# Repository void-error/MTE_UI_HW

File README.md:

# MTE_UI_HW
User Interface hardware common to all Modular Test Equipment projects

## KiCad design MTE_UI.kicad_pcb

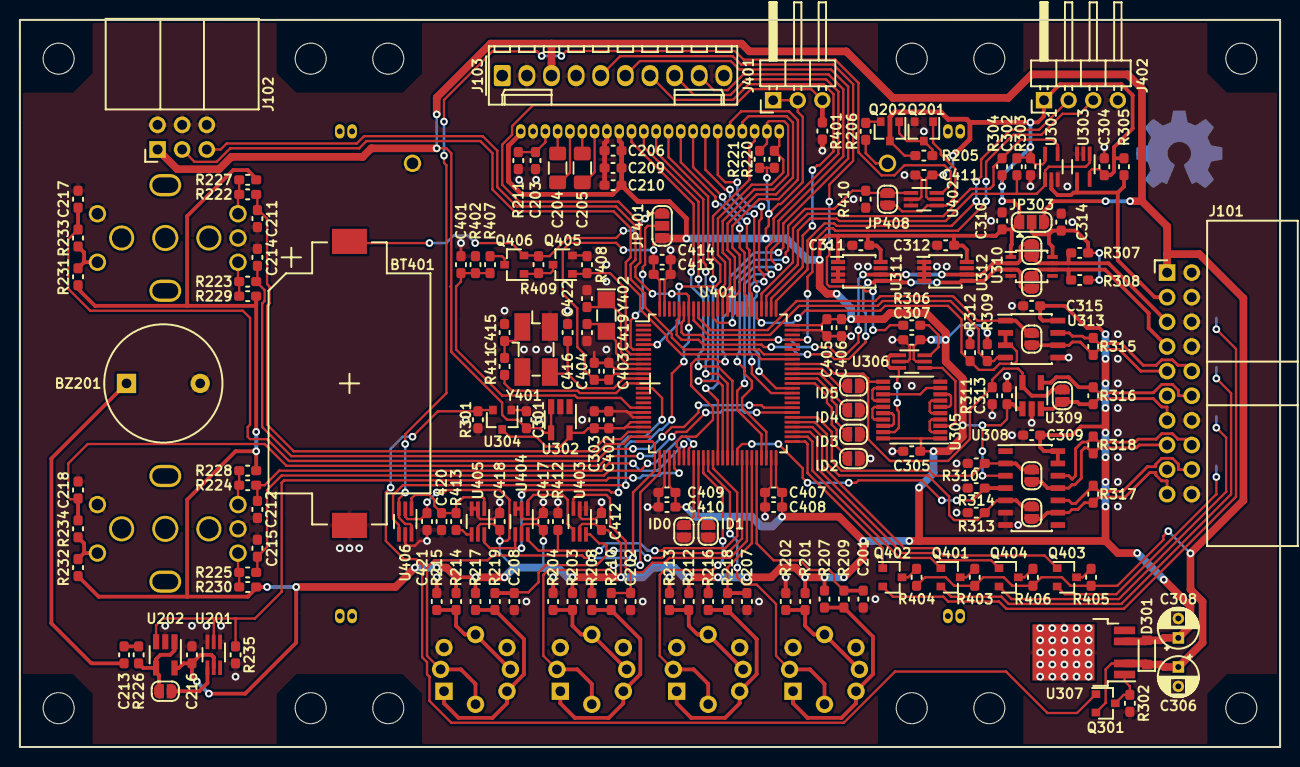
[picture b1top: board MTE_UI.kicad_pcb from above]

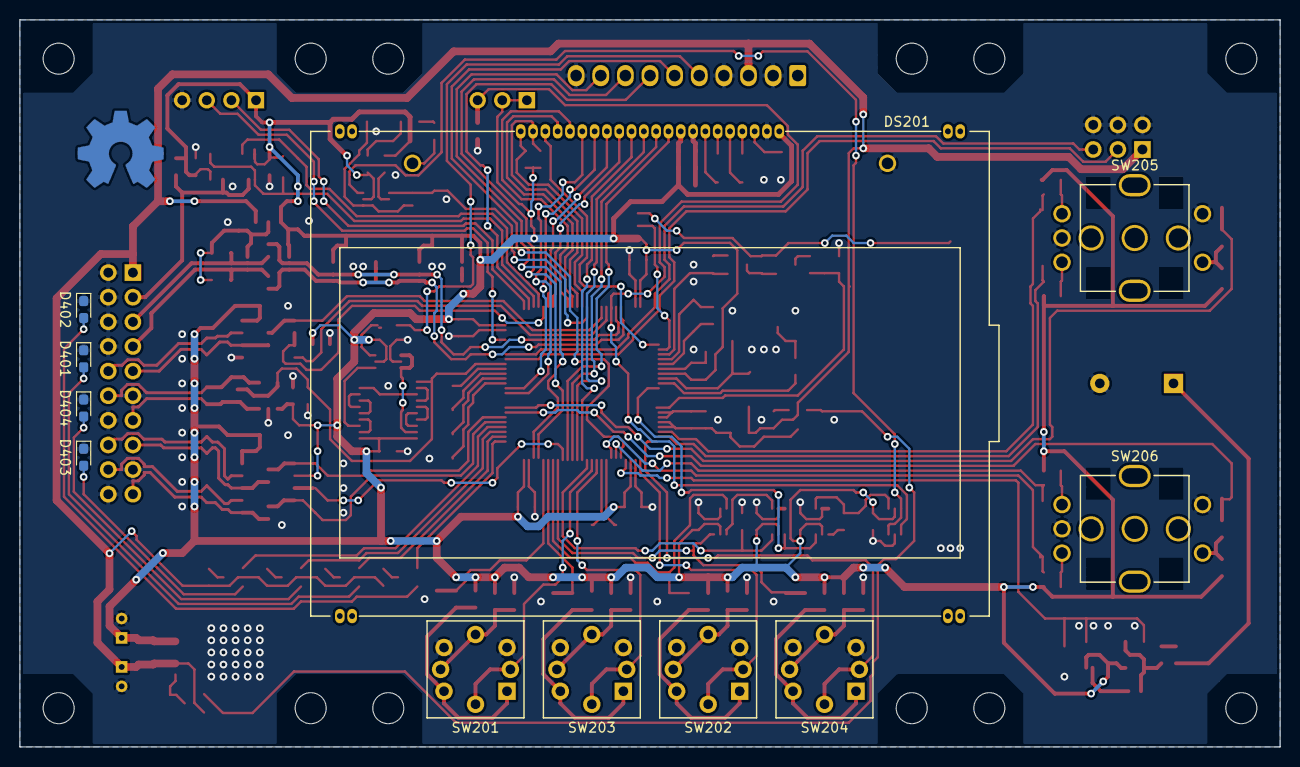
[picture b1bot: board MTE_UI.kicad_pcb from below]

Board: 2 copper layers, 130.0 x 75.0 mm, 201 parts (12 on the bottom side), 140 nets.

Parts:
BT401: Battery_Cell; BatteryHolder_Keystone_1060_1x2032
BZ201: Buzzer; Buzzer_12x9.5RM7.6
C201, C202, C207, C208, C211, C212, C214, C215, C217, C218, C401, C402: 10n; C_0603_1608Metric_Pad1.05x0.95mm_HandSolder
C203: 330n; C_0603_1608Metric_Pad1.05x0.95mm_HandSolder
C204, C205: 2u2; C_1206_3216Metric_Pad1.42x1.75mm_HandSolder
C206, C216, C302, C304, C305, C307, C309, C310, C311, C312, C313, C314, C315, C403, C405, C407, C409, C411, C412, C413, C417, C418, C421: 100n; C_0603_1608Metric_Pad1.05x0.95mm_HandSolder
C209, C210, C213, C301, C404, C406, C408, C410, C414, C420: 4u7; C_0603_1608Metric_Pad1.05x0.95mm_HandSolder
C303: 1u; C_0603_1608Metric_Pad1.05x0.95mm_HandSolder
C306, C308: 10u; CP_Radial_D4.0mm_P2.00mm
C415, C422: 12p; C_0603_1608Metric_Pad1.05x0.95mm_HandSolder
C416, C419: 22p; C_0603_1608Metric_Pad1.05x0.95mm_HandSolder
D301: BAS316; D_SOD-323_HandSoldering
D401, D402, D403, D404: LED; LED_0603_1608Metric_Pad1.05x0.95mm_HandSolder
DS201: ERC-12864-655; ERC12864-655
J101: Conn_02x10_Odd_Even; IDC-Header_2x10_P2.54mm_Horizontal
J102: Conn_02x03_Odd_Even; IDC-Header_2x03_P2.54mm_Horizontal
J103: Conn_01x10; Molex_KK-254_AE-6410-10A_1x10_P2.54mm_Vertical
J401: Conn_01x03; PinHeader_1x03_P2.54mm_Horizontal
J402: Conn_01x04; PinHeader_1x04_P2.54mm_Horizontal
JP201, JP301, JP302, JP304, JP305, JP306, JP307, JP402, JP403, JP404, JP405, JP406, JP407, JP408: SolderJumper_2_Open; SolderJumper-2_P1.3mm_Open_RoundedPad1.0x1.5mm
JP303, JP401: SolderJumper_3_Open; SolderJumper-3_P1.3mm_Open_RoundedPad1.0x1.5mm
LOGO101: Logo_Open_Hardware_Small; OSHW-Symbol_8.9x8mm_Copper
MK101, MK102, MK103, MK104, MK105, MK106, MK107, MK108, MK109, MK110, MK111, MK112: MountingHole; MountingHole_3.2mm_M3
Q201, Q401, Q402, Q403, Q404, Q405: BSS138; SOT-23
Q202, Q301, Q406: BSS84; SOT-23
R201, R202, R203, R204, R212, R213, R214, R215: 1k5; R_0603_1608Metric_Pad1.05x0.95mm_HandSolder
R205, R207, R208, R216, R217, R227, R228, R229, R230, R231, R232, R401, R413: 33k; R_0603_1608Metric_Pad1.05x0.95mm_HandSolder
R206: 10R; R_0603_1608Metric_Pad1.05x0.95mm_HandSolder
R209, R210, R218, R219, R222, R223, R224, R225, R233, R234, R305, R307, R308, R403, R404, R405, R406: 3k3; R_0603_1608Metric_Pad1.05x0.95mm_HandSolder
R211: 1M; R_0603_1608Metric_Pad1.05x0.95mm_HandSolder
R220, R221, R235, R303, R304, R309, R310, R311, R312, R313, R314, R408, R409, R410, R412: 100k; R_0603_1608Metric_Pad1.05x0.95mm_HandSolder
R226, R306, R315, R316, R317, R318: 100R; R_0603_1608Metric_Pad1.05x0.95mm_HandSolder
R301, R302: R; R_0603_1608Metric_Pad1.05x0.95mm_HandSolder
R402, R407: 10k; R_0603_1608Metric_Pad1.05x0.95mm_HandSolder
R411: 180R; R_0603_1608Metric_Pad1.05x0.95mm_HandSolder
SW201, SW202, SW203, SW204: B3W-9000-RG2N; SW_TH_Tactile_Omron_B3W-9000
SW205, SW206: Rotary_Encoder_Switch; SW_TH_Encoding_Alps_EC11K-S
U201: 74LVC1G125; SOT-363_SC-70-6_Handsoldering
U202: TLV271; SOT-23-5_HandSoldering
U301: 74LVC1G126; SOT-353_SC-70-5_Handsoldering
U302: LM4132-2; SOT-23-5_HandSoldering
U303: 74LVC1G125; SOT-353_SC-70-5_Handsoldering
U304: STM809T; SOT-23
U305: 74LVC273; TSSOP-20_4.4x6.5mm_P0.65mm
U306, U406: 74LVC2G14; SOT-363_SC-70-6_Handsoldering
U307: NCP5661DT33; TO-252-4
U308: SN65MLVD203; SOIC-14_3.9x8.7mm_P1.27mm
U309: SN65LVDS1; SOT-23-5_HandSoldering
U310: PCA9509DP; TSSOP-8_3x3mm_P0.65mm
U311, U312: 24LC16; MSOP-8_3x3mm_P0.65mm
U313: SN65MLVD200A; SOIC-8_3.9x4.9mm_P1.27mm
U401: STM32F101VDTx; LQFP-100_14x14mm_P0.5mm
U402, U403, U404, U405: 74LVC1G57; SOT-363_SC-70-6_Handsoldering
Y401: 8MHz; Crystal_SMD_EuroQuartz_MJ-4Pin_5.0x3.2mm_HandSoldering
Y402: 32.768kHz; Crystal_SMD_EuroQuartz_EQ161-2Pin_3.2x1.5mm_HandSoldering

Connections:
+3V3A: C303.1, C402.1, U302.5, U304.3, U401.21, U401.22
+3V3D: C206.1, C209.1, C210.1, C216.2, C302.2, C304.2, C305.2, C307.2, C308.1, C309.2, C310.2, C311.2, C312.2, C313.2, C315.2, C403.2, C404.2, C405.2, C406.2, C407.2, C408.2, C409.2, C410.2, C411.2, C412.2, C413.2, C414.2, C417.2, C418.2, C421.2, D301.2, DS201.14, DS201.22, J401.1, J401.2, J402.1, JP303.1, JP401.3, Q202.3, R201.1, R203.1, R205.1, R207.1, R208.1, R212.1, R214.1, R216.1, R217.1, R220.1, R221.1, R227.1, R228.1, R229.1, R230.1, R231.1, R232.1, R303.1, R304.1, R305.1, R309.1, U201.5, U202.5, U301.5, U303.5, U305.1, U305.20, U306.5, U307.4, U308.3, U308.13, U308.14, U309.1, U310.1, U311.1, U311.8, U312.8, U313.8, U401.11, U401.28, U401.50, U401.75, U401.100, U402.5, U403.5, U404.5, U405.5, U406.2
+5V0D: C301.2, C306.1, D301.1, J101.1, J102.1, J103.3, JP303.3, Q301.2, R403.2, R404.2, R405.2, R406.1, U302.3, U302.4, U307.2
/BUS_1-WIRE: J101.3, R305.2, U301.2, U303.4
/BUS_CLKR_N: J101.13, JP305.2, R316.2, U309.3
/BUS_CLKR_P: J101.12, R316.1, U309.4
/BUS_RX_N: J101.15, JP307.2, R318.2, U308.11
/BUS_RX_P: J101.16, R318.1, U308.12
/BUS_SCL: J101.5, JP302.2, R307.2, U310.7
/BUS_SDA: J101.7, JP301.2, R308.2, U310.6
/BUS_TRIG_N: J101.10, R315.2, U313.7
/BUS_TRIG_P: J101.9, JP304.2, R315.1, U313.6
/BUS_TX_N: J101.18, R317.2, U308.10
/BUS_TX_P: J101.19, JP306.2, R317.1, U308.9
/EXT_RX: J102.5, U401.69
/EXT_TX: J102.3, U401.68
/FAN0_RPM: J103.8, U401.47
/FAN1_RPM: J103.9, U401.48
/FAN_PWM: J103.7, U401.77
/Microcontroller/1W-RX: R304.2, U301.4, U401.79
/Microcontroller/1W-TX: R303.2, U301.1, U303.1, U401.78
/Microcontroller/ACT_1-WIRE: Q403.1, U401.54
/Microcontroller/ACT_I2C: Q404.1, U401.53
/Microcontroller/ACT_UART_EXT: Q401.1, U401.52
/Microcontroller/ACT_UART_INT: Q402.1, U401.51
/Microcontroller/BOOT0: J401.3, R401.1, U401.94, U406.4
/Microcontroller/BZ: R235.1, U201.2, U202.3, U401.29
/Microcontroller/CLKR: JP305.1, R311.2, U305.11, U309.5, U401.67
/Microcontroller/ENC1_A: C211.1, R222.2, U401.23
/Microcontroller/ENC1_B: C214.1, R223.2, U401.24
/Microcontroller/ENC1_S: C217.1, R233.1, U401.58
/Microcontroller/ENC2_A: C212.1, R224.2, U401.31
/Microcontroller/ENC2_B: C215.1, R225.2, U401.32
/Microcontroller/ENC2_S: C218.1, R234.1, U401.57
/Microcontroller/EN_VBAT: Q405.1, R408.2, U401.7
/Microcontroller/ID0: JP402.1, U401.33
/Microcontroller/ID1: JP403.1, U401.34
/Microcontroller/ID2: JP404.1, U401.63
/Microcontroller/ID3: JP405.1, U401.64
/Microcontroller/ID4: JP406.1, U401.65
/Microcontroller/ID5: JP407.1, U401.66
/Microcontroller/LCD_BL: JP408.2, Q201.1, U402.4
/Microcontroller/LCD_C|D: DS201.3, U401.5
/Microcontroller/LCD_D0: DS201.6, U401.61
/Microcontroller/LCD_D1: DS201.7, U401.62
/Microcontroller/LCD_D2: DS201.8, U401.81
/Microcontroller/LCD_D3: DS201.9, U401.82
/Microcontroller/LCD_D4: DS201.10, U401.38
/Microcontroller/LCD_D5: DS201.11, U401.39
/Microcontroller/LCD_D6: DS201.12, U401.40
/Microcontroller/LCD_D7: DS201.13, U401.41
/Microcontroller/LCD_RD: DS201.5, U401.85
/Microcontroller/LCD_WR: DS201.4, U401.86
/Microcontroller/LCD_~CS~: DS201.1, R220.2, U401.88
/Microcontroller/LCD_~RST~: DS201.2, R221.2, U401.87
/Microcontroller/NRST: U401.14, U404.4, U405.6
/Microcontroller/OSC32_IN: C422.1, U401.8, Y402.1
/Microcontroller/OSC32_OUT: C419.1, U401.9, Y402.2
/Microcontroller/OSC_IN: C416.1, U401.12, Y401.3
/Microcontroller/OSC_OUT: R411.1, U401.13
/Microcontroller/RX: JP307.1, R310.1, U308.2, U401.56
/Microcontroller/SCL: JP302.1, U310.2, U311.6, U312.6, U401.95
/Microcontroller/SDA: JP301.1, U310.3, U311.5, U312.5, U401.96
/Microcontroller/SW1: C208.1, R219.1, U401.43, U403.6
/Microcontroller/SW1_BL: SW204.6, SW204.7, U401.25
/Microcontroller/SW2: C202.1, R210.1, U401.44, U403.3
/Microcontroller/SW2_BL: SW202.6, SW202.7, U401.26
/Microcontroller/SW3: C207.1, R218.1, U401.45
/Microcontroller/SW3_BL: SW203.6, SW203.7, U401.35
/Microcontroller/SW4: C201.1, R209.1, U401.46
/Microcontroller/SW4_BL: SW201.6, SW201.7, U401.36
/Microcontroller/SWCLK: J402.2, U401.76
/Microcontroller/SWDIO: J402.3, U401.72
/Microcontroller/TRIG_DIR: R312.1, U313.2, U313.3, U401.80
/Microcontroller/TRIG_IN: JP304.1, U313.1, U401.92
/Microcontroller/TRIG_OUT: R309.2, U313.4, U401.93
/Microcontroller/TX: JP306.1, R313.2, U308.5, U401.55
/Microcontroller/TX_EN: R314.2, U308.4, U401.42
/Microcontroller/UMON_VBAT: C401.1, R402.1, R407.2, U401.18
/Microcontroller/~EN_BOOT~: R412.1, U401.37, U404.6
/PG: J103.6, U401.30
/Peripherals/D0: U305.3, U306.4
/Peripherals/D1: U305.2, U305.4
/Peripherals/D2: U305.5, U305.7
/Peripherals/D3: U305.6, U305.8
/Peripherals/D4: U305.9, U305.13
/Peripherals/D5: U305.12, U305.14
/Peripherals/D6: U305.15, U305.17
/Peripherals/D7: U305.16, U305.18
/SYNC: J103.5, R306.1
DGND: BT401.2, BZ201.2, C201.2, C202.2, C203.2, C206.2, C207.2, C208.2, C209.2, C210.2, C211.2, C212.2, C214.2, C215.2, C216.1, C217.2, C218.2, C301.1, C302.1, C303.2, C304.1, C305.1, C306.2, C307.1, C308.2, C309.1, C310.1, C311.1, C312.1, C313.1, C314.1, C315.1, C401.2, C402.2, C403.1, C404.1, C405.1, C406.1, C407.1, C408.1, C409.1, C410.1, C411.1, C412.1, C413.1, C414.1, C415.2, C416.2, C417.1, C418.1, C419.2, C420.1, C421.1, C422.2, D401.1, D402.1, D403.1, D404.1, DS201.15, DS201.21, DS201.32, J101.2, J101.4, J101.6, J101.8, J101.11, J101.14, J101.17, J101.20, J102.2, J102.4, J102.6, J103.2, J103.4, J103.10, J402.4, JP402.2, JP403.2, JP404.2, JP405.2, JP406.2, JP407.2, Q201.2, Q405.2, R202.2, R204.2, R211.2, R213.2, R215.2, R235.2, R301.2, R302.2, R310.2, R311.1, R312.2, R313.1, R314.1, R401.2, R402.2, R408.1, R410.2, R412.2, SW201.3, SW201.4, SW202.3, SW202.4, SW203.3, SW203.4, SW204.3, SW204.4, SW205.C, SW205.S2, SW206.C, SW206.S2, U201.1, U201.3, U202.2, U301.3, U302.2, U303.2, U303.3, U304.1, U305.10, U306.2, U307.3, U308.6, U308.7, U309.2, U310.4, U311.2, U311.3, U311.4, U311.7, U312.1, U312.2, U312.3, U312.4, U312.7, U313.5, U401.10, U401.19, U401.20, U401.27, U401.49, U401.74, U401.99, U402.2, U402.3, U403.1, U403.2, U404.2, U404.3, U405.2, U405.3, U406.5, Y401.2, Y401.4
unnamed: BT401.1, JP401.1, Q406.2, R409.1
unnamed: BZ201.1, C213.2
unnamed: C203.1, DS201.20, R211.1
unnamed: C204.1, DS201.19
unnamed: C204.2, DS201.18
unnamed: C205.1, DS201.16
unnamed: C205.2, DS201.17
unnamed: C213.1, R226.1
unnamed: C314.2, JP303.2, R307.1, R308.1, U310.8
unnamed: C415.1, R411.2, Y401.1
unnamed: C420.2, R413.1, U405.1, U406.1
unnamed: D401.2, Q401.2
unnamed: D402.2, Q402.2
unnamed: D403.2, Q403.2
unnamed: D404.2, Q404.2
unnamed: DS201.31, R206.1
unnamed: JP201.1, R226.2, U202.1, U202.4
unnamed: JP201.2, U201.4
unnamed: JP401.2, U401.6
unnamed: JP408.1, R410.1, U401.89, U402.1
unnamed: Q201.3, Q202.1, R205.2
unnamed: Q202.2, R206.2
unnamed: Q301.1, R301.1, U304.2
unnamed: Q301.3, R302.1, U307.1
unnamed: Q401.3, R403.1
unnamed: Q402.3, R404.1
unnamed: Q403.3, R405.1
unnamed: Q404.3, R406.2
unnamed: Q405.3, Q406.1, R409.2
unnamed: Q406.3, R407.1
unnamed: R201.2, R202.1, SW201.5, SW201.8
unnamed: R203.2, R204.1, SW202.5, SW202.8
unnamed: R207.2, R209.2, SW201.1, SW201.2
unnamed: R208.2, R210.2, SW202.1, SW202.2
unnamed: R212.2, R213.1, SW203.5, SW203.8
unnamed: R214.2, R215.1, SW204.5, SW204.8
unnamed: R216.2, R218.2, SW203.1, SW203.2
unnamed: R217.2, R219.2, SW204.1, SW204.2
unnamed: R222.1, R227.2, SW205.A
unnamed: R223.1, R229.2, SW205.B
unnamed: R224.1, R228.2, SW206.A
unnamed: R225.1, R230.2, SW206.B
unnamed: R231.2, R233.2, SW205.S1
unnamed: R232.2, R234.2, SW206.S1
unnamed: R306.2, U306.6
unnamed: R413.2, U405.4
unnamed: U305.19, U306.1, U306.3
unnamed: U402.6, U406.3, U406.6
unnamed: U403.4, U404.1

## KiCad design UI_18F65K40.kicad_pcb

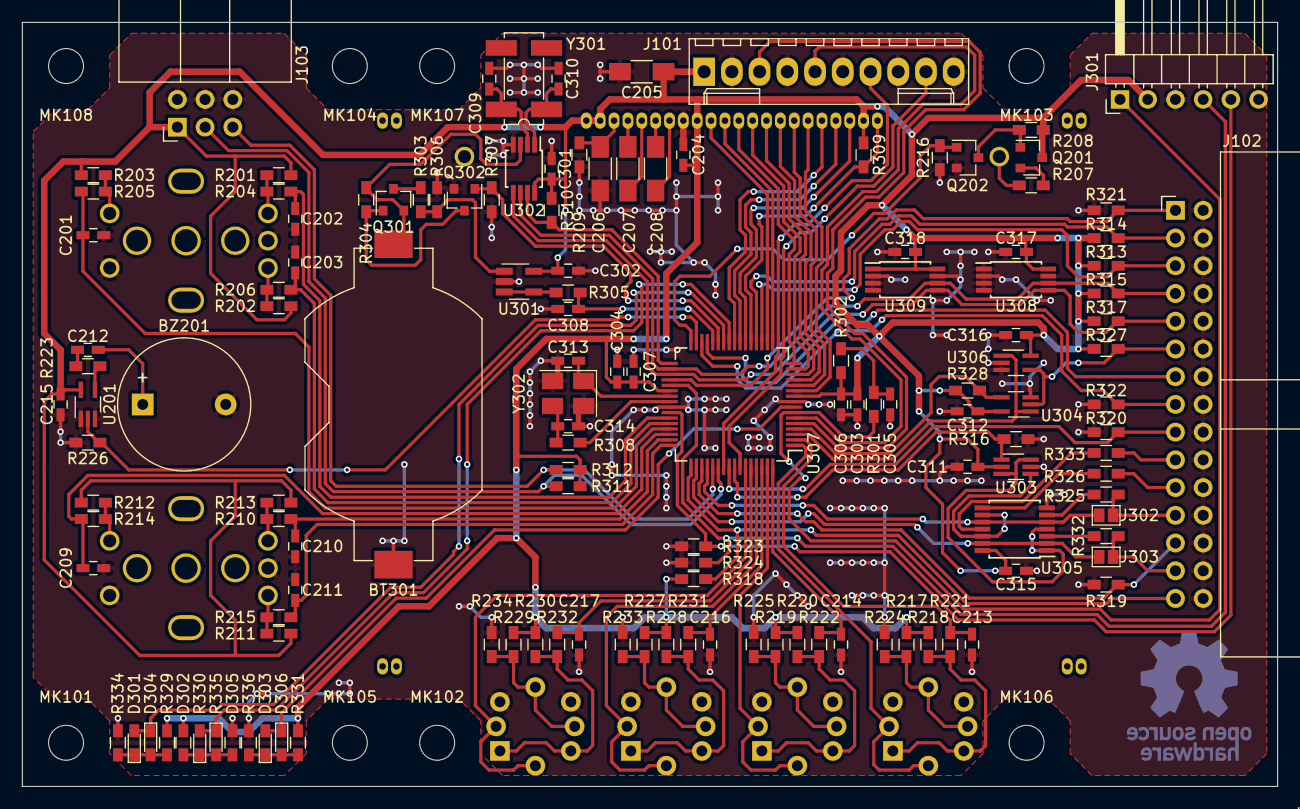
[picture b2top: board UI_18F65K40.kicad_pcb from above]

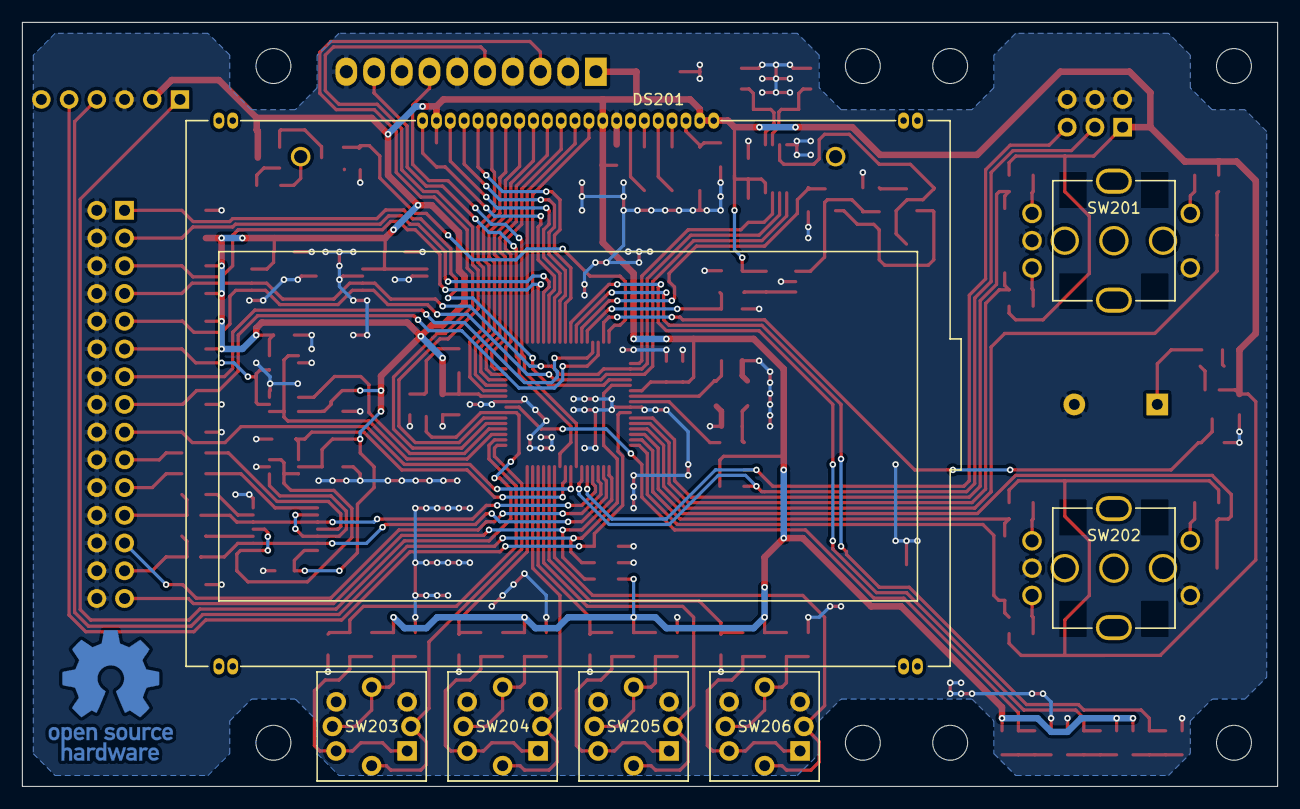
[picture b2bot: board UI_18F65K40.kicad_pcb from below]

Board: 2 copper layers, 115.0 x 70.0 mm, 153 parts (8 on the bottom side), 110 nets.

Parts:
BT301: CR2032; Keystone_1058_1x2032-CoinCell
BZ201: Buzzer; Buzzer_12x9.5RM7.6
C201, C202, C203, C209, C210, C211, C213, C214, C216, C217, C305, C308: 10n; C_0603_HandSoldering
C204, C212, C215, C301, C302, C306, C307, C311, C312, C315, C316, C317, C318: 100n; C_0603_HandSoldering
C205: 10u; C_1206_HandSoldering
C206: 330n; C_1206_HandSoldering
C207, C208: 2u2; C_1206_HandSoldering
C303, C304: 1u; C_0603_HandSoldering
C309, C310: 12p; C_0603_HandSoldering
C313, C314: 15p; C_0603_HandSoldering
D301, D302, D303, D304, D305, D306: LED; LED_0603_HandSoldering
DS201: ERC-12864-655; ERC12864-655
J101: MOLEX_KK-254; Molex_KK-6410-10_10x2.54mm_Straight
J102: IDC 2x15; IDC-Header_2x15_P2.54mm_Horizontal
J103: IDC 2x3; IDC-Header_2x03_P2.54mm_Horizontal
J301: Pin_Header_01x06; Pin_Header_Angled_1x06_Pitch2.54mm
J302, J303: GS2
LOGO101: OSHW; OSHW-Logo_11.4x12mm_Copper
LOGO201, LOGO301: OSHW; Dummy_Empty
MK101, MK102, MK103, MK104, MK105, MK106, MK107, MK108: Mounting_Hole; MountingHole_3.2mm_M3
Q201, Q301: BSS84; SOT-23
Q202, Q302: BSS138; SOT-23
R201, R202, R203, R210, R211, R212, R218, R220, R228, R230, R302: 10k; R_0603_HandSoldering
R204, R205, R206, R213, R214, R215, R217, R219, R221, R222, R227, R229, R231, R232, R301, R305, R319, R320: 1k; R_0603_HandSoldering
R207: 33R; R_0603_HandSoldering
R208, R311, R312, R313, R314, R315, R317, R327: 3k3; R_0603_HandSoldering
R209: 10M; R_0603_HandSoldering
R216, R226, R303, R306, R316, R318, R321, R322, R323, R324: 100k; R_0603_HandSoldering
R223, R308, R325, R326, R332, R333: 100R; R_0603_HandSoldering
R224, R225, R233, R234, R329, R330, R331, R334, R335, R336: 1k5; R_0603_HandSoldering
R304, R307, R309, R310, R328: 33k; R_0603_HandSoldering
SW201, SW202: EC11K1524402; SW_TH_Encoding_Alps_EC11K-S
SW203, SW204, SW205, SW206: B3W-9000-RG2N; SW_TH_Tactile_Omron_B3W-9000
U201, U306: 74LVC1G125; SOT-353_SC-70-5_Handsoldering
U301: MCP6V81U; SOT-23-5_HandSoldering
U302: MCP79410; MSOP-8_3x3mm_Pitch0.65mm
U303: 74LVC2G14; SOT-363_SC-70-6_Handsoldering
U304: 74LVC1G126; SOT-353_SC-70-5_Handsoldering
U305: 74HC08; TSSOP-14_4.4x5mm_Pitch0.65mm
U307: PIC18F65K40-I/PT; TQFP-64_10x10mm_Pitch0.5mm
U308, U309: 24LC512; TSSOP-8_4.4x3mm_Pitch0.65mm
Y301: 32.768kHz; Crystal_SMD_SeikoEpson_MC306-4pin_8.0x3.2mm_HandSoldering
Y302: 16MHz; Crystal_SMD_EuroQuartz_MT-4pin_3.2x2.5mm_HandSoldering

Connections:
/Microcontroller & Peripherals/1-WIRE-RX: R328.2, U304.4, U307.4
/Microcontroller & Peripherals/1-WIRE-TX: U304.1, U306.1, U307.3
/Microcontroller & Peripherals/ACT_595_SPI: D303.2, D306.1, U307.8
/Microcontroller & Peripherals/ACT_I2C_1-WIRE: D302.2, D305.1, U307.25
/Microcontroller & Peripherals/ACT_UART: D301.2, D304.1, U307.26
/Microcontroller & Peripherals/BL: Q202.1, R216.1, U307.32
/Microcontroller & Peripherals/BL_SW1: SW203.6, SW203.7, U307.1
/Microcontroller & Peripherals/BL_SW2: SW204.6, SW204.7, U307.63
/Microcontroller & Peripherals/BL_SW3: SW205.6, SW205.7, U307.61
/Microcontroller & Peripherals/BL_SW4: SW206.6, SW206.7, U307.59
/Microcontroller & Peripherals/BUS_1-WIRE: J102.11, R327.2, U304.2, U306.4
/Microcontroller & Peripherals/BUS_CLKR: J102.1, R321.2, U307.36
/Microcontroller & Peripherals/BUS_GPI: J102.15, R322.2, U307.30
/Microcontroller & Peripherals/BUS_GPO: J102.13, U307.29
/Microcontroller & Peripherals/BUS_MISO: J102.25, R319.2, U307.51
/Microcontroller & Peripherals/BUS_MOSI: J102.23, J302.2, R325.2
/Microcontroller & Peripherals/BUS_QS: J102.21, R326.2
/Microcontroller & Peripherals/BUS_RX: J102.3, R314.2, U307.20
/Microcontroller & Peripherals/BUS_SCL: J102.7, R315.2, U302.6, U307.34, U308.6, U309.6
/Microcontroller & Peripherals/BUS_SCLK: J102.27, J303.2, R332.2
/Microcontroller & Peripherals/BUS_SDA: J102.9, R317.2, U302.5, U307.35, U308.5, U309.5
/Microcontroller & Peripherals/BUS_SH_CP: J102.19, R333.2
/Microcontroller & Peripherals/BUS_ST_CP: J102.17, R320.2, U307.56
/Microcontroller & Peripherals/BUS_TX: J102.5, R313.2, U307.19
/Microcontroller & Peripherals/BUS_~CS~: J102.29, R318.2, U307.49
/Microcontroller & Peripherals/BZ: R226.1, U201.2, U307.31
/Microcontroller & Peripherals/ENC1_A: C202.1, R204.2, U307.43
/Microcontroller & Peripherals/ENC1_B: C203.1, R206.2, U307.44
/Microcontroller & Peripherals/ENC1_S: C201.1, R205.1, U307.45
/Microcontroller & Peripherals/ENC2_A: C210.1, R213.2, U307.47
/Microcontroller & Peripherals/ENC2_B: C211.1, R215.2, U307.48
/Microcontroller & Peripherals/ENC2_S: C209.1, R214.1, U307.46
/Microcontroller & Peripherals/EN_VBAT: Q302.1, R307.2, U307.27
/Microcontroller & Peripherals/EXT_RX: J103.3, R311.2, U307.54
/Microcontroller & Peripherals/EXT_TX: J103.5, R312.2, U307.53
/Microcontroller & Peripherals/FAN_PWM: J101.5, U307.6
/Microcontroller & Peripherals/FAN_RPM0: J101.7, U307.55
/Microcontroller & Peripherals/FAN_RPM1: J101.9, U307.58
/Microcontroller & Peripherals/ICSPCLK: J301.5, R323.2, U307.42
/Microcontroller & Peripherals/ICSPDAT: J301.4, R324.2, U307.37
/Microcontroller & Peripherals/LCD_C|D: DS201.3, U307.22
/Microcontroller & Peripherals/LCD_D0: DS201.6, U307.11
/Microcontroller & Peripherals/LCD_D1: DS201.7, U307.12
/Microcontroller & Peripherals/LCD_D2: DS201.8, U307.13
/Microcontroller & Peripherals/LCD_D3: DS201.9, U307.14
/Microcontroller & Peripherals/LCD_D4: DS201.10, U307.15
/Microcontroller & Peripherals/LCD_D5: DS201.11, U307.16
/Microcontroller & Peripherals/LCD_D6: DS201.12, U307.17
/Microcontroller & Peripherals/LCD_D7: DS201.13, U307.18
/Microcontroller & Peripherals/LCD_E: DS201.5, U307.24
/Microcontroller & Peripherals/LCD_R|~W~: DS201.4, U307.23
/Microcontroller & Peripherals/LCD_~CS~: DS201.1, R309.2, U307.21
/Microcontroller & Peripherals/MFP: R310.2, U302.7, U307.33
/Microcontroller & Peripherals/OSC1: C313.1, U307.39, Y302.1
/Microcontroller & Peripherals/OSC2: R308.1, U307.40
/Microcontroller & Peripherals/SENSE_VBAT: C308.1, R305.2, U307.28
/Microcontroller & Peripherals/SW1: C213.1, R221.1, U307.2
/Microcontroller & Peripherals/SW2: C214.1, R222.1, U307.64
/Microcontroller & Peripherals/SW3: C216.1, R231.1, U307.62
/Microcontroller & Peripherals/SW4: C217.1, R232.1, U307.60
/Microcontroller & Peripherals/SYNC: J101.3, U307.5
/Microcontroller & Peripherals/VPP: J301.1, R301.2, U307.7
GND: BT301.2, BZ201.2, C201.2, C202.2, C203.2, C204.2, C205.2, C206.2, C209.2, C210.2, C211.2, C213.2, C214.2, C215.1, C216.2, C217.2, C301.1, C302.1, C303.1, C304.1, C305.2, C306.1, C307.1, C308.2, C309.2, C310.2, C311.1, C312.1, C313.2, C314.2, C315.1, C316.1, C317.1, C318.1, DS201.15, DS201.32, J101.2, J101.4, J101.6, J101.8, J101.10, J102.2, J102.4, J102.6, J102.8, J102.10, J102.12, J102.14, J102.16, J102.18, J102.20, J102.22, J102.24, J102.26, J102.28, J102.30, J103.2, J103.4, J103.6, J301.3, Q202.2, Q302.2, R209.2, R216.2, R224.2, R225.2, R226.2, R233.2, R234.2, R306.2, R307.1, R316.1, R319.1, R320.1, R321.1, R322.1, R323.1, R324.1, R334.2, R335.2, R336.2, SW201.2, SW201.6, SW202.2, SW202.6, SW203.3, SW203.4, SW204.3, SW204.4, SW205.3, SW205.4, SW206.3, SW206.4, U201.1, U201.3, U301.2, U302.4, U303.5, U304.3, U305.7, U306.2, U306.3, U307.9, U307.41, U308.1, U308.2, U308.3, U308.4, U308.7, U309.2, U309.3, U309.4, U309.7, Y302.2, Y302.4
unnamed: BT301.1, Q301.2, R304.1, U302.3
unnamed: BZ201.1, C212.2
unnamed: C206.1, DS201.20, R209.1
unnamed: C207.1, DS201.19
unnamed: C207.2, DS201.18
unnamed: C208.1, DS201.16
unnamed: C208.2, DS201.17
unnamed: C212.1, R223.1
unnamed: C305.1, R301.1, R302.1
unnamed: C309.1, U302.2, Y301.4
unnamed: C310.1, U302.1, Y301.1
unnamed: C314.1, R308.2, Y302.3
unnamed: D301.1, D304.2, R329.2, R334.1
unnamed: D302.1, D305.2, R330.2, R335.1
unnamed: D303.1, D306.2, R331.2, R336.1
unnamed: DS201.31, R207.1
unnamed: J302.1, U305.5, U305.10, U307.52
unnamed: J303.1, U305.2, U305.13, U307.50
unnamed: Q201.1, Q202.3, R208.2
unnamed: Q201.2, R207.2
unnamed: Q301.1, Q302.3, R304.2
unnamed: Q301.3, R303.1
unnamed: R201.2, R204.1, SW201.1
unnamed: R202.2, R206.1, SW201.3
unnamed: R203.2, R205.2, SW201.7
unnamed: R210.2, R213.1, SW202.1
unnamed: R211.2, R215.1, SW202.3
unnamed: R212.2, R214.2, SW202.7
unnamed: R217.2, R224.1, SW203.5, SW203.8
unnamed: R218.2, R221.2, SW203.1, SW203.2
unnamed: R219.2, R225.1, SW204.5, SW204.8
unnamed: R220.2, R222.2, SW204.1, SW204.2
unnamed: R223.2, U201.4
unnamed: R227.2, R233.1, SW205.5, SW205.8
unnamed: R228.2, R231.2, SW205.1, SW205.2
unnamed: R229.2, R234.1, SW206.5, SW206.8
unnamed: R230.2, R232.2, SW206.1, SW206.2
unnamed: R303.2, R306.1, U301.1
unnamed: R305.1, U301.3, U301.4
unnamed: R316.2, U303.1, U307.57
unnamed: R325.1, U305.6
unnamed: R326.1, U305.8
unnamed: R332.1, U305.3
unnamed: R333.1, U305.11
unnamed: U303.3, U303.6, U305.1, U305.4
unnamed: U303.4, U305.9, U305.12
VBUS: C204.1, C205.1, C215.2, C301.2, C302.2, C303.2, C304.2, C306.2, C307.2, C311.2, C312.2, C315.2, C316.2, C317.2, C318.2, DS201.2, DS201.14, DS201.21, DS201.22, J101.1, J103.1, J301.2, Q201.3, R201.1, R202.1, R203.1, R208.1, R210.1, R211.1, R212.1, R217.1, R218.1, R219.1, R220.1, R227.1, R228.1, R229.1, R230.1, R302.2, R309.1, R310.1, R311.1, R312.1, R313.1, R314.1, R315.1, R317.1, R318.1, R327.1, R328.1, R329.1, R330.1, R331.1, U201.5, U301.5, U302.8, U303.2, U304.5, U305.14, U306.5, U307.10, U307.38, U308.8, U309.1, U309.8

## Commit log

2018-02-25 Added KiCad project files, license, schematic in PDF format
2018-02-26 Updated pdf schematic file
2018-02-26 Rearranged bus connector pins Updated PDF schematic
2018-03-04 Added netlist, PCB layout
2018-03-04 Updated PDF schematic
2018-03-04 Removed useless via from the VPP net near R301
2018-03-15 Flipped Q301 since it was backwards, updated netlist, PCB layout, PDF schematic
2018-11-25 Made too many changes, please ignore
2018-11-25 Removed junk, updated PDF
2019-12-27 Revised schematic, initial PCB layout complete
2019-12-27 Fixed library references
2019-12-29 Renamed file
2019-12-29 Rename MTE.dcm to mte.dcm
2019-12-29 Renaming stuff the hard way
2019-12-29 Renamed stuff the hard way

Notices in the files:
MTE_UI.kicad_pcb:
License: TAPR Open Hardware License - https://www.tapr.org/ohl
